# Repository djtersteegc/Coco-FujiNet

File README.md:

Find all the CocoFuji needs in the main Fujinet hardware repo now, https://github.com/FujiNetWIFI/fujinet-hardware

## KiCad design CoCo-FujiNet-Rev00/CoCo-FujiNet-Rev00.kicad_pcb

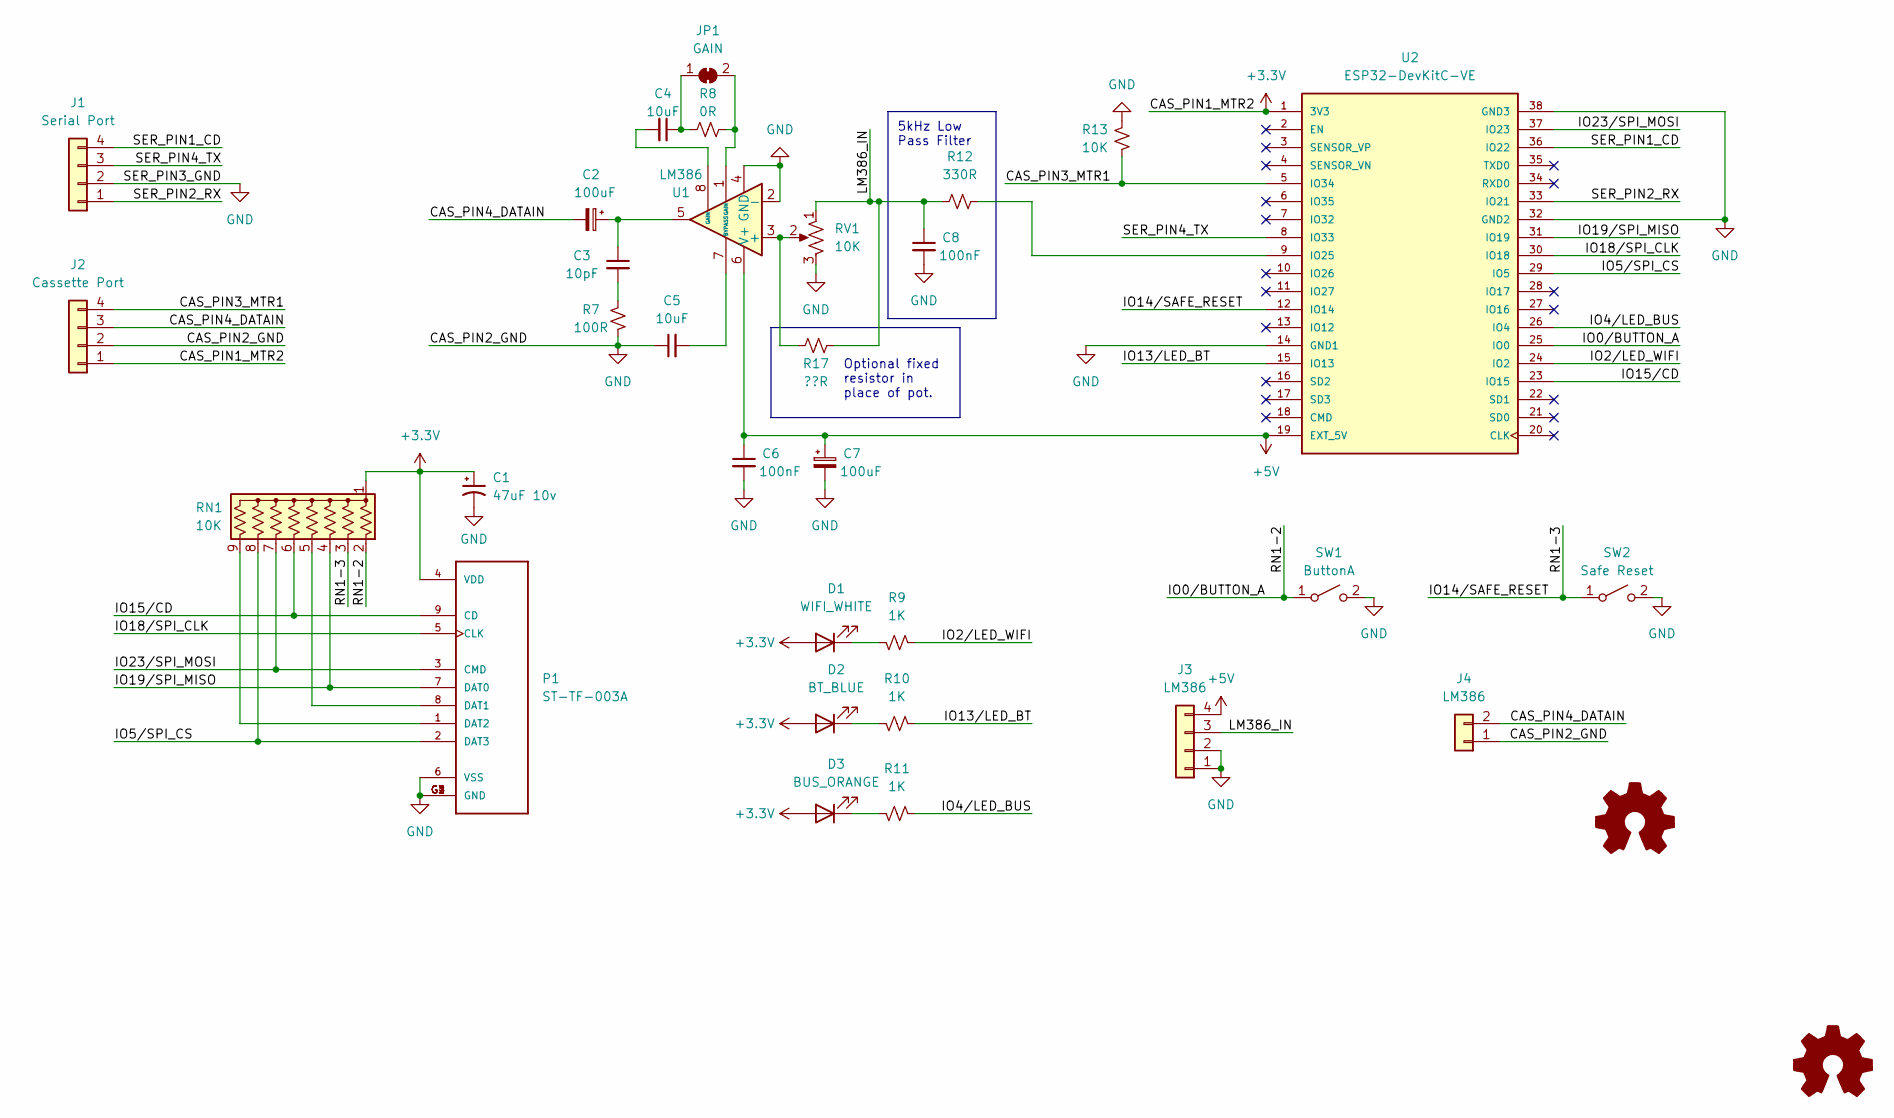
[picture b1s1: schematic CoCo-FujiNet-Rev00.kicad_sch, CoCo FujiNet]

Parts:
C1: 47uF 10v; CP_EIA-3528-15_AVX-H_Pad1.50x2.35mm_HandSolder
C2, C7: 100uF; CP_Radial_D6.3mm_P2.50mm
C3: 10pF; C_Disc_D5.0mm_W2.5mm_P5.00mm
C4, C5: 10uF; C_Disc_D5.0mm_W2.5mm_P5.00mm
C6, C8: 100nF; C_Disc_D5.0mm_W2.5mm_P5.00mm
D1: WIFI_WHITE; LED_D3.0mm
D2: BT_BLUE; LED_D3.0mm
D3: BUS_ORANGE; LED_D3.0mm
J1: Serial Port; PinHeader_1x04_P2.54mm_Vertical
J2: Cassette Port; PinHeader_1x04_P2.54mm_Vertical
J3: LM386; PinHeader_1x04_P2.54mm_Vertical
J4: LM386; PinHeader_1x02_P2.54mm_Vertical
JP1: GAIN; SolderJumper-2_P1.3mm_Bridged_RoundedPad1.0x1.5mm
P1: ST-TF-003A; SUNTECH_ST-TF-003A
R7: 100R; R_Axial_DIN0207_L6.3mm_D2.5mm_P7.62mm_Horizontal
R8: 0R; R_Axial_DIN0207_L6.3mm_D2.5mm_P7.62mm_Horizontal
R9, R10, R11: 1K; R_Axial_DIN0207_L6.3mm_D2.5mm_P7.62mm_Horizontal
R12: 330R; R_Axial_DIN0207_L6.3mm_D2.5mm_P7.62mm_Horizontal
R13: 10K; R_Axial_DIN0207_L6.3mm_D2.5mm_P7.62mm_Horizontal
R17: ??R; R_Axial_DIN0207_L6.3mm_D2.5mm_P7.62mm_Horizontal
RN1: 10K; R_Array_SIP9
RV1: 10K; Potentiometer_Runtron_RM-065_Vertical
SW1: ButtonA; SW_PUSH_6mm_H5mm
SW2: Safe Reset; SW_PUSH_6mm_H5mm
U1: LM386; DIP-8_W7.62mm_Socket
U2: ESP32-DevKitC-VE; MODULE_ESP32-DEVKITC-32U; PARTREV N/A

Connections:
+3.3V: C1.1, D1.2 (A), D2.2 (A), D3.2 (A), J2.1, P1.4 (VDD), RN1.1 (common), U2.1 (3V3)
+5V: C6.1, C7.1, J3.4, U1.6 (V+), U2.19 (EXT_5V)
/CAS_PIN3_MTR1: J2.4, R13.1, U2.5 (IO34)
/CAS_PIN4_DATAIN: C2.2, J2.3, J4.2
/IO0/BUTTON_A: RN1.2 (R1), SW1.1 (A), U2.25 (IO0)
/IO2/LED_WIFI: R9.2, U2.24 (IO2)
/IO4/LED_BUS: R11.2, U2.26 (IO4)
/IO5/SPI_CS: P1.2 (DAT3), RN1.8 (R7), U2.29 (IO5)
/IO13/LED_BT: R10.2, U2.15 (IO13)
/IO14/SAFE_RESET: RN1.3 (R2), SW2.1 (A), U2.12 (IO14)
/IO15/CD: P1.9 (CD), RN1.6 (R5), U2.23 (IO15)
/IO18/SPI_CLK: P1.5 (CLK), U2.30 (IO18)
/IO19/SPI_MISO: P1.7 (DAT0), RN1.4 (R3), U2.31 (IO19)
/IO23/SPI_MOSI: P1.3 (CMD), RN1.7 (R6), U2.37 (IO23)
/LM386_IN: C8.1, J3.3, R12.1, R17.2, RV1.1
/SER_PIN1_CD: J1.4, U2.36 (IO22)
/SER_PIN2_RX: J1.1, U2.33 (IO21)
/SER_PIN4_TX: J1.3, U2.8 (IO33)
GND: C1.2, C5.1, C6.2, C7.2, C8.2, J1.2, J2.2, J3.1, J3.2, J4.1, P1.6 (VSS), P1.G1 (GND), P1.G2 (GND), P1.G3 (GND), P1.G4 (GND), R7.1, R13.2, RV1.3, SW1.2 (B), SW2.2 (B), U1.2 (-), U1.4 (GND), U2.14 (GND1), U2.32 (GND2), U2.38 (GND3)
unnamed: C2.1, C3.1, U1.5
unnamed: C3.2, R7.2
unnamed: C4.2, U1.8 (GAIN)
unnamed: D1.1 (K), R9.1
unnamed: D2.1 (K), R10.1
unnamed: D3.1 (K), R11.1
unnamed: C4.1, JP1.1 (A), R8.1
unnamed: JP1.2 (B), R8.2, U1.1 (GAIN)
unnamed: P1.8 (DAT1), RN1.5 (R4)
unnamed: P1.1 (DAT2), RN1.9 (R8)
unnamed: R17.1, RV1.2, U1.3 (+)
unnamed: C5.2, U1.7 (BYPASS)
unnamed: R12.2, U2.9 (IO25)

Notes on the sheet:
5kHz Low Pass Filter
Optional fixed resistor in place of pot.

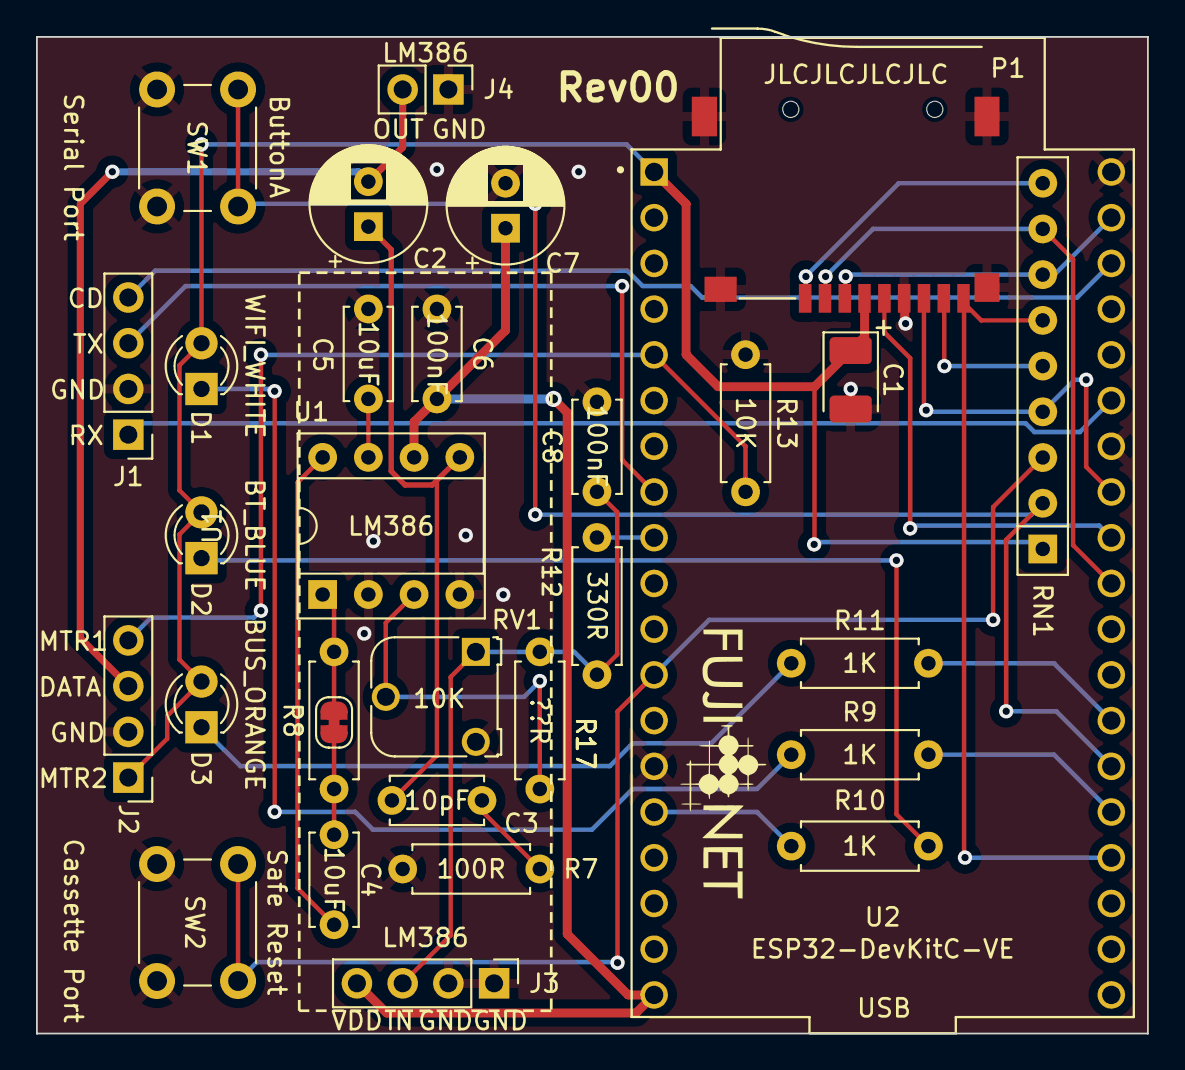
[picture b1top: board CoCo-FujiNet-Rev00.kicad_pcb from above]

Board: 2 copper layers, 61.7 x 55.4 mm, 31 parts (0 on the bottom side), 32 nets.

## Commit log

2024-01-12 Rev0 sent to JLC
2024-01-20 Add Rev00
2024-01-20 Add some Rev00 docs
2024-01-25 Add KiCad PCB image
2024-02-25 Update build docs
2024-03-04 Add Rev000 files and update docs
2024-03-17 Update 3D files and docs for VIE antenna option
2025-02-03 Remove and redirect to Fujinet hardware repo
